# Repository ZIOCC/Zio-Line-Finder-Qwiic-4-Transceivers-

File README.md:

# Zio Line Finder (Qwiic 4 Transceivers)

> This product can be available for purchase [here](https://www.smart-prototyping.com/Zio-Line-Finder-Qwiic-4-Transceivers).

#### Description
This is a Qwiic I2C version of a line-following sensor array, intended especially for building robots that take advantage of I2C for communication between subsystems.

Like other line-following sensor modules, it has four IR reflectance-sensing sub-modules that can detect a line’s position. We use a PCA9539A I/O expander to detect when a given sub-module’s output voltage crosses its logic-level threshold, indicating the detection of the line. If one of the sub-module I/O channels is driven LOW, that’s where the line is.

There are four potentiometers to independently adjust the IR modules’ sensitivities to suit different robot platforms, accounting for differences in sensor mounting heights. There are four LEDs that provide a visual indicator for the detection status of each channel, which makes it easy to tune the sensitivity of each sensor channel.
Because the PCA9539A has 16 digital I/O channels, we’ve broken out the other 12 channels to standard-pitch pin-headers so you can take advantage of them as you see fit.

#### Specification

* Four Channel IR Sensors
* I2C sensor: PCA9539A
* I2C address:0x74-0x77 (Default:0x74)
* Differential Comparator IC: LM339DR
* Extra Digital Sensor Channel: 12 Channels
* Dimension: 47.2x 36.5mm
* Weight: Main board: 7.4g, IR sensor board: 0.9g

#### Links

* [Eagle File and Schematic](https://github.com/ZIOCC/Zio-Line-Finder-Qwiic-4-Transceivers-)
* [PCA9539 Library and Example Code](https://www.smart-prototyping.com/image/data/NOA-RnD/101904%20line%20finder/Zio_Line_Finder_Library.zip)
* [PCA9539 Datasheet](http://www.ti.com/lit/ds/symlink/pca9539.pdf)
* [LM339DR Datasheet](http://www.ti.com/lit/ds/snosbj3e/snosbj3e.pdf)

> ###### About Zio
> Zio is a new line of open sourced, compact, and grid layout boards, fully integrated for Arduino and Qwiic ecosystem. Designed ideally for wearables, robotics, small-space limitations or other on the go projects. Check out other awesome Zio products [here](https://www.smart-prototyping.com/Zio).

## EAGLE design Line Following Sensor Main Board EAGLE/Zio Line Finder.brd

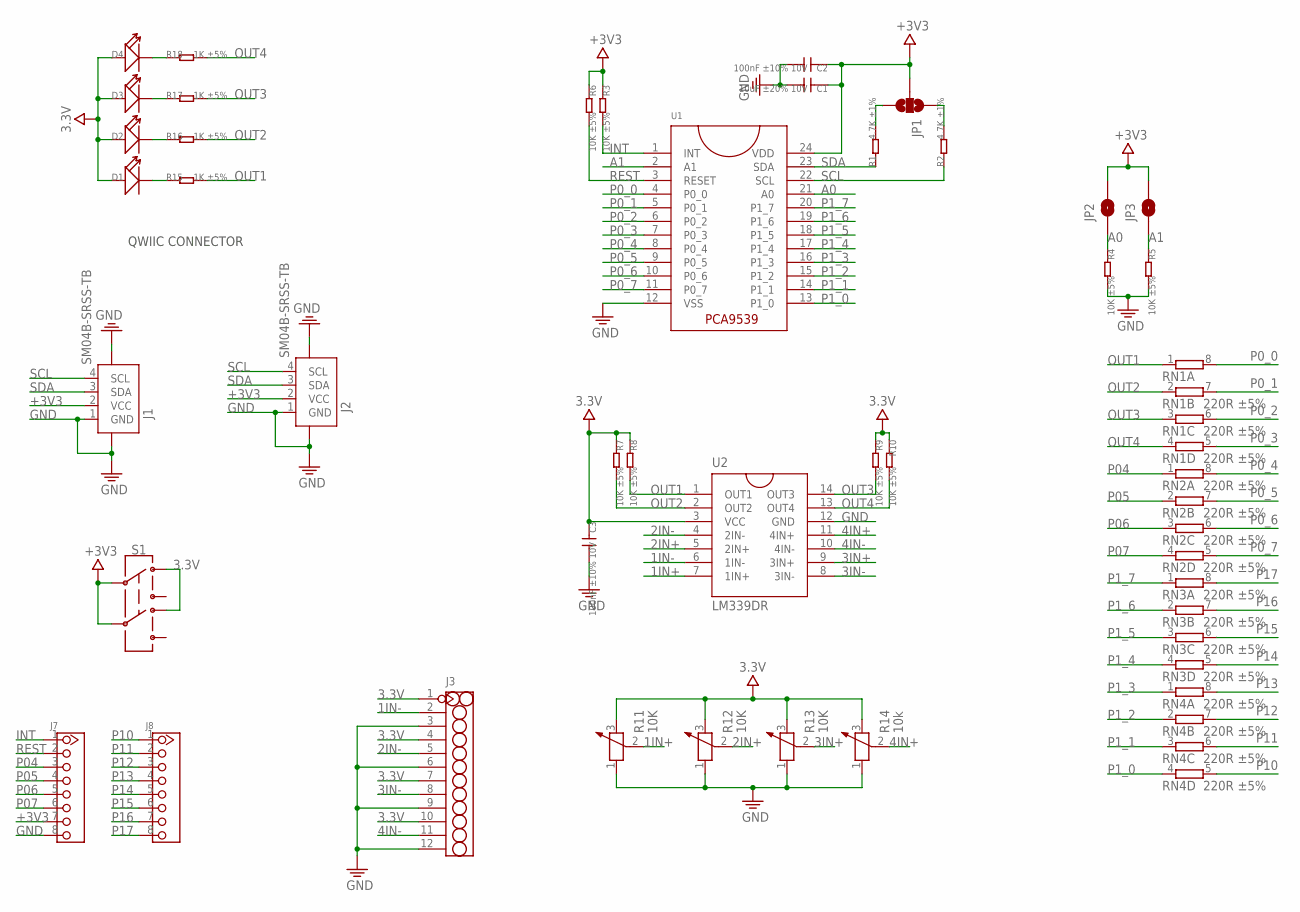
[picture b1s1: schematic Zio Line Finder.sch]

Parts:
C1: 10uF ±20% 10V; 0603
C2, C3: 100nF ±10% 10V; 0603
D1, D2, D3, D4: LED'0603'; LED-0603
J1, J2: SM04B-SRSS-TB; JST-SH-4P
J3: HEADER-12P-2.54; 12P-2.54
J7, J8: HEADER-8P-60/35MIL; 8P-2.54-60/35MIL
JP1: JUMPER-SMT_3_2-NC_PASTE_NOCREM; SMT-JUMPER_3_2-NC_PASTE_SILK_NOCREM
JP2, JP3: JUMPER-SMT_2_NC_PASTE_NOCREM; SMT-JUMPER_2_NC_PASTE_SILK_NOCREM
R1, R2: 4.7K ±1%; 0402
R3, R4, R5, R6, R7, R8, R9, R10: 10K ±5%; 0402
R11, R12, R13: 10K; 3P-SQUA-7X6.8
R14: 10k; 3P-SQUA-7X6.8
R15, R16, R17, R18: 1K ±5%; 0402
RN1, RN2, RN3, RN4: 220R ±5%; RESISTOR-DIL_0603-ARV
S1: SWITCH-DPDT-SMD-AYZ0202; SWITCH_DPDT_SMD_AYZ0202
U1: PCA9539; TSSOP24
U2: LM339DR; SOIC14-8.7

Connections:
1IN+: R11.2, U2.7 (1IN+)
1IN-: J3.2, U2.6 (1IN-)
2IN+: R12.2, U2.5 (2IN+)
2IN-: J3.5, U2.4 (2IN-)
3.3V: C3.1, D1.+, D2.+, D3.+, D4.+, J3.1, J3.4, J3.7, J3.10, R7.1, R8.1, R9.1, R10.1, R11.3, R12.3, R13.3, R14.3, S1.1, S1.4, U2.3 (VCC)
3IN+: R13.2, U2.9 (3IN+)
3IN-: J3.8, U2.8 (3IN-)
4IN+: R14.2, U2.11 (4IN+)
4IN-: J3.11, U2.10 (4IN-)
+3V3: C1.1, C2.1, J1.2 (VCC), J2.2 (VCC), J7.7, JP1.2, JP2.2, JP3.2, R3.1, R6.1, S1.2, S1.5, U1.24 (VDD)
A0: JP2.1, R4.1, U1.21 (A0)
A1: JP3.1, R5.1, U1.2 (A1)
GND: C1.2, C2.2, C3.2, J1.1 (GND), J1.NC1 (5), J1.NC2 (6), J2.1 (GND), J2.NC1 (5), J2.NC2 (6), J3.3, J3.6, J3.9, J3.12, J7.8, R4.2, R5.2, R11.1, R12.1, R13.1, R14.1, U1.12 (VSS), U2.12 (GND)
INT: J7.1, R3.2, U1.1 (INT)
unnamed: D1.-, R15.1
unnamed: D2.-, R16.1
unnamed: D3.-, R17.1
unnamed: D4.-, R18.1
unnamed: JP1.3, R1.2
unnamed: JP1.1, R2.2
OUT1: R8.2, R15.2, RN1.1, U2.1 (OUT1)
OUT2: R7.2, R16.2, RN1.2 (1), U2.2 (OUT2)
OUT3: R9.2, R17.2, RN1.3 (1), U2.14 (OUT3)
OUT4: R10.2, R18.2, RN1.4 (1), U2.13 (OUT4)
P0_0: RN1.8 (2), U1.4 (P0_0)
P0_1: RN1.7 (2), U1.5 (P0_1)
P0_2: RN1.6 (2), U1.6 (P0_2)
P0_3: RN1.5 (2), U1.7 (P0_3)
P0_4: RN2.8 (2), U1.8 (P0_4)
P0_5: RN2.7 (2), U1.9 (P0_5)
P0_6: RN2.6 (2), U1.10 (P0_6)
P0_7: RN2.5 (2), U1.11 (P0_7)
P1_0: RN4.4 (1), U1.13 (P1_0)
P1_1: RN4.3 (1), U1.14 (P1_1)
P1_2: RN4.2 (1), U1.15 (P1_2)
P1_3: RN4.1, U1.16 (P1_3)
P1_4: RN3.4 (1), U1.17 (P1_4)
P1_5: RN3.3 (1), U1.18 (P1_5)
P1_6: RN3.2 (1), U1.19 (P1_6)
P1_7: RN3.1, U1.20 (P1_7)
P04: J7.3, RN2.1
P05: J7.4, RN2.2 (1)
P06: J7.5, RN2.3 (1)
P07: J7.6, RN2.4 (1)
P10: J8.1, RN4.5 (2)
P11: J8.2, RN4.6 (2)
P12: J8.3, RN4.7 (2)
P13: J8.4, RN4.8 (2)
P14: J8.5, RN3.5 (2)
P15: J8.6, RN3.6 (2)
P16: J8.7, RN3.7 (2)
P17: J8.8, RN3.8 (2)
REST: J7.2, R6.2, U1.3 (RESET)
SCL: J1.4 (SCL), J2.4 (SCL), R2.1, U1.22 (SCL)
SDA: J1.3 (SDA), J2.3 (SDA), R1.1, U1.23 (SDA)

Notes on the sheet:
QWIIC CONNECTOR

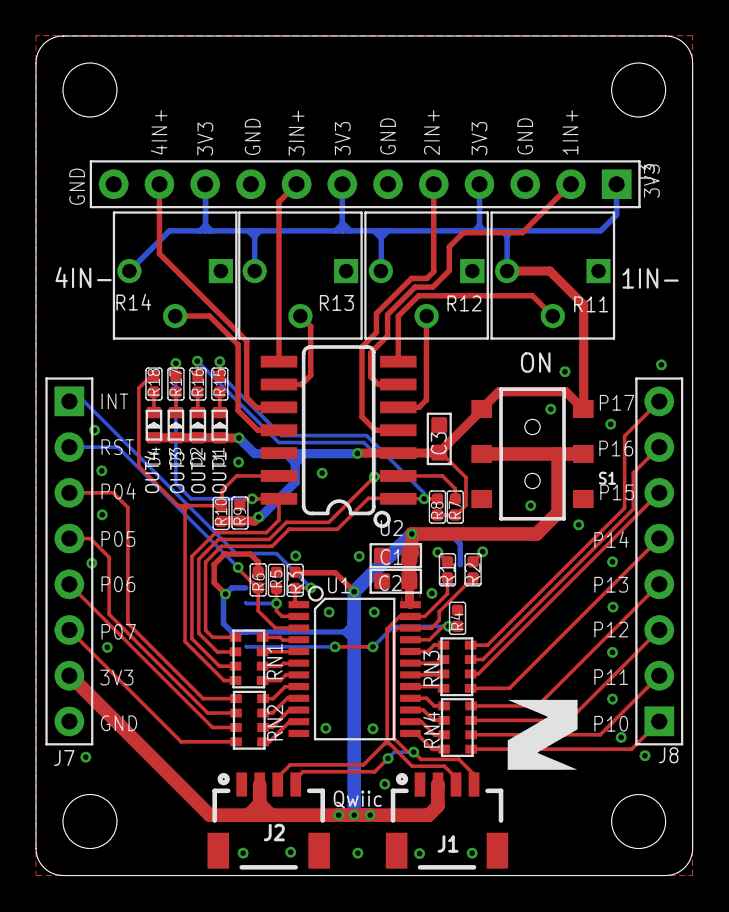
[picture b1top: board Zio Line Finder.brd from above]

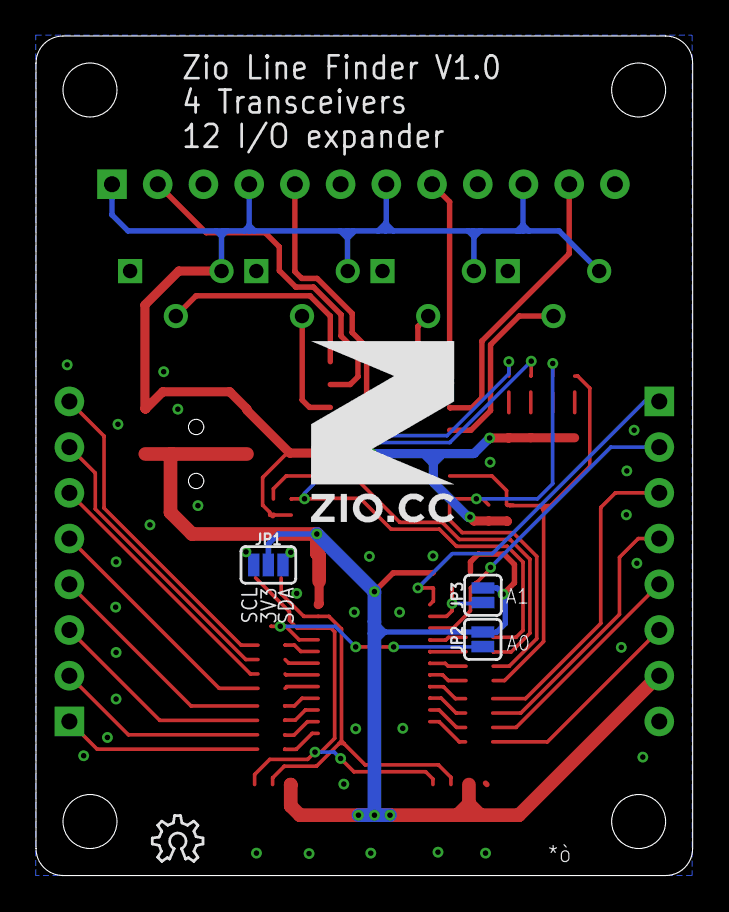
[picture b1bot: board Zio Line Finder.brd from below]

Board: 2 copper layers, 36.5 x 46.6 mm, 43 parts (5 on the bottom side), 55 nets.

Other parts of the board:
U$6: 10MM
U$7: OSHW_6X100_NOTEXT
U$8: 6MM

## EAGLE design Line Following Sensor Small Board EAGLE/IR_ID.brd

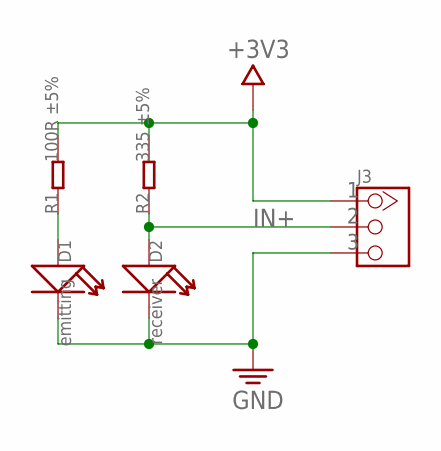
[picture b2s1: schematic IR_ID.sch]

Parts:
D1: emitting; LED-2P-2.54-6MM
D2: receiver; LED-2P-2.54-6MM
J3: HEADER-3P-2.54; 3P-2.54
R1: 100R ±5%; 0402
R2: 335 ±5%; 0402

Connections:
+3V3: J3.1, R1.2, R2.2
GND: D1.-, D2.-, J3.3
IN+: D2.+, J3.2, R2.1
unnamed: D1.+, R1.1

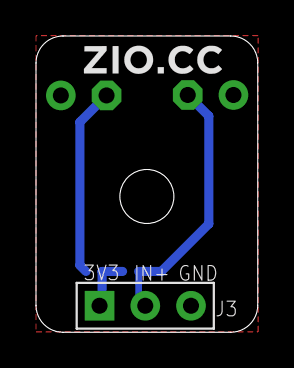
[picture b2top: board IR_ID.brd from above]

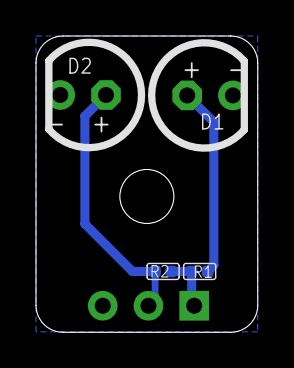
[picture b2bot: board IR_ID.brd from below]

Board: 2 copper layers, 12.3 x 16.5 mm, 6 parts (4 on the bottom side), 4 nets.

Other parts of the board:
U$1: 1.5MM

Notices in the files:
parts and their libraries:
SparkFun-Switches: Licensing: Creative Commons ShareAlike 4.0 International - https://creativecommons.org/licenses/by-sa/4.0
